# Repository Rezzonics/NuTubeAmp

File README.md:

# NuTubeAmp (EAGLE 6.3.0)
NuTube 6P1 25W Hybrid Amplifier

Eagle CAD 6.3.0:
- Eagle CAD Schematics (.sch)
- Eagle CAD Layout (.brd)
- Bill of Materials (txt, csv, xlsx)
- Components library (.lbr)

FreeCAD 16.0:
 - 3D CAD NuTube box (NuTube / 12AX7)

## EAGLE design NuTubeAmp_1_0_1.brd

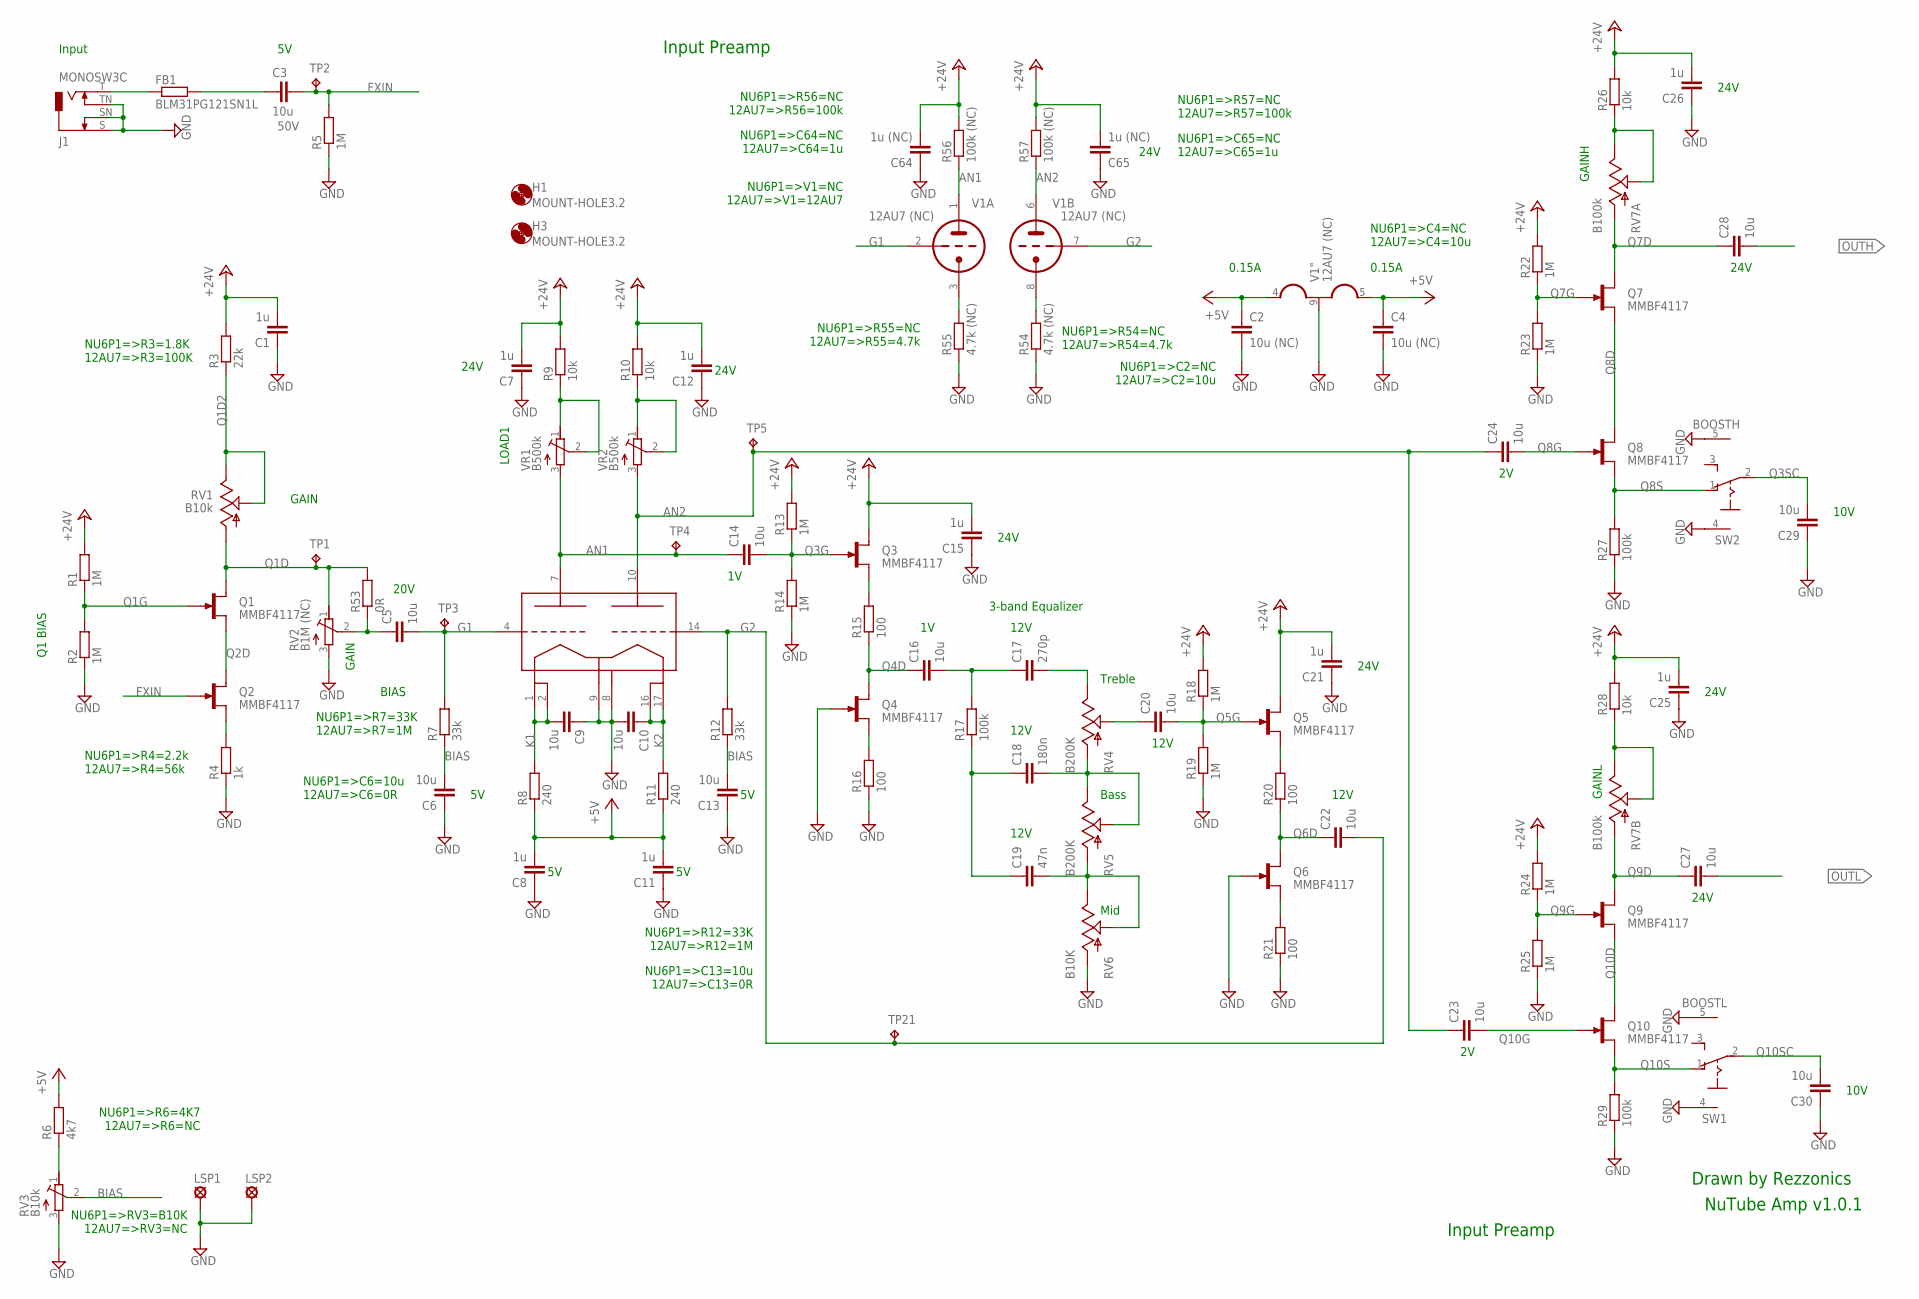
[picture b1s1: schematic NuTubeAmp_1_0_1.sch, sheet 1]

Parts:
C1, C7, C8, C11, C12, C15, C21, C25, C26: 1u; C0603K; MPN C1608X5R1H105K080AB
C2, C4: 10u (NC); C0805K; MPN GRM21BR6YA106KE43L
C3, C5, C6, C9, C10, C13, C14, C16, C20, C22, C23, C24, C27, C28, C29, C30: 10u; C0805K; MPN GRM21BR6YA106KE43L
C17: 270p; C0402K; MPN GRM1555C1H271JA01D
C18: 180n; C0603K; MPN GRM188R71C184KA01D
C19: 47n; C0402K; MPN GRM155R71H473KE14D
C64, C65: 1u (NC); C0603K; MPN C1608X5R1H105K080AB
FB1: BLM31PG121SN1L; R1206; MPN BLM31PG121SN1L
H1, H3: MOUNT-HOLE3.2; 3,2; MPN *
J1: MONOSW3C; NEUTRIK-NMJ4HCD2; MPN NMJ4HCD2
LSP1, LSP2: LSP13; MPN 1249
Q1, Q2, Q3, Q4, Q5, Q6, Q7, Q8, Q9, Q10: MMBF4117; SOT23; MPN MMBF4117
R1, R2, R5, R13, R14, R18, R19, R22, R23, R24, R25: 1M; R0402; MPN ERJ-2RKF1004X
R3: 22k; R0402; MPN ERJ-2RKF1801X
R4: 1k; R0402; MPN ERJ-2RKF2201X
R6: 4k7; R0402; MPN ERJ-2RKF4701X
R7, R12: 33k; R0402; MPN ERJ-2RKF3302X
R8, R11: 240; R0603; MPN ERJ-3EKF2400V
R9, R10, R26, R28: 10k; R0402; MPN ERJ-2RKF1002X
R15, R16, R20, R21: 100; R0402; MPN ERJ-2RKF1000X
R17, R27, R29: 100k; R0402; MPN ERJ-2RKF1003X
R53: 0R; R0402; MPN ERJ-2GE0R00X
R54, R55: 4.7k (NC); R0402; MPN ERJ-2RKF4701X
R56, R57: 100k (NC); R0402; MPN ERJ-2RKF1003X
RV1: B10k; 3310Y; MPN 3310Y-001-103L
RV2: B1M (NC); RTRIM3314G; MPN 3314G-1-105E
RV3: B10k; RTRIM3314G; MPN 3314G-2-103E
RV4, RV5: B200K; 3310Y; MPN 3310Y-001-204L
RV6: B10K; 3310Y; MPN 3310Y-001-103L
RV7: B100k; 3310H; MPN 3310H-001-104L
SW1: BOOSTL; MHS122K; MPN MHS122K
SW2: BOOSTH; MHS122K; MPN MHS122K
TP1, TP2, TP3, TP4, TP5, TP21: TPTP10R; TP10R; MPN *
U1: NUTUBE 6P1; NUTUBE_6P1_1; MPN *
V1: 12AU7 (NC); VT9; MPN *
VR1, VR2: B500k; RTRIM3314G; MPN 3314G-1-504E

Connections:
+5V: C2.1, C4.1, C8.2, C11.2, R6.2, R8.1, R11.1, V1.4 (H1), V1.5 (H3); also elsewhere on the board
+24V: C1.2, C7.2, C12.2, C15.2, C21.2, C25.2, C26.2, C64.2, C65.2, Q3.1 (D), Q5.1 (D), R1.2, R3.2, R9.2, R10.2, R13.2, R18.2, R22.2, R24.2, R26.2, R28.2, R56.2, R57.2; also elsewhere on the board
AN1: C14.1, R56.1, TP4.TP, U1.7 (A1_7), V1.1 (TA), VR1.3 (A)
AN2: C23.1, C24.1, R57.1, TP5.TP, U1.10 (A2_10), V1.6 (TA), VR2.3 (A)
BAST: C18.2, RV4.P$1 (A), RV5.P$2 (S), RV5.P$3 (E)
BIAS: C6.2, C13.2, R7.1, R12.1, RV3.2 (S)
EQIN: C16.2, C17.1, R17.2
EQOUT: C20.1, RV4.P$2 (S)
FXIN: C3.2, Q2.2 (G), R5.2, TP2.TP
G1: C5.2, R7.2, TP3.TP, U1.4 (G1_4), V1.2 (TG)
G2: C22.2, R12.2, TP21.TP, U1.14 (G2_14), V1.7 (TG)
G2TOP: R55.2, V1.3 (TK)
G3TOP: R26.1, RV7.P$2 (S), RV7.P$3 (E)
G4TOP: R28.1, RV7.P$5 (S), RV7.P$6 (E)
GND: C1.1, C2.2, C4.2, C6.1, C7.1, C8.1, C9.1, C10.2, C11.1, C12.1, C13.1, C15.1, C21.1, C25.1, C26.1, C29.1, C30.1, C64.1, C65.1, J1.S, J1.SN, J1.TN, LSP1.MP, LSP2.MP, Q4.2 (G), Q6.2 (G), R2.1, R4.1, R5.1, R14.1, R16.1, R19.1, R21.1, R23.1, R25.1, R27.1, R29.1, R54.1, R55.1, RV2.3 (A), RV3.3 (A), RV6.P$1 (A), SW1.4 (G1), SW1.5 (G2), SW2.4 (G1), SW2.5 (G2), U1.8 (GND_8), U1.9 (F2_9), V1.9 (H2); also elsewhere on the board
GTOP: C5.1, R53.1, RV2.2 (S)
K1: C9.2, R8.2, U1.1 (F1_1), U1.2 (F1_2)
K2: C10.1, R11.2, U1.16 (F3_16), U1.17 (F3_17)
MIDT: C19.2, RV5.P$1 (A), RV6.P$2 (S), RV6.P$3 (E)
unnamed: FB1.1, J1.T
unnamed: C3.1, FB1.2
unnamed: Q3.3 (S), R15.2
unnamed: R6.1, RV3.1 (E)
unnamed: R54.2, V1.8 (TK)
unnamed: C18.1, C19.1, R17.1
OUTH: C28.2; also elsewhere on the board
OUTL: C27.2; also elsewhere on the board
Q1D: Q1.1 (D), R53.2, RV1.P$1 (A), RV2.1 (E), TP1.TP
Q1D2: R3.1, RV1.P$2 (S), RV1.P$3 (E)
Q1G: Q1.2 (G), R1.1, R2.2
Q1S: Q2.3 (S), R4.2
Q1S1: Q4.3 (S), R16.2
Q1S2: Q6.3 (S), R21.2
Q2D: Q1.3 (S), Q2.1 (D)
Q3G: C14.2, Q3.2 (G), R13.1, R14.2
Q3SC: C29.2, SW2.2
Q4D: C16.1, Q4.1 (D), R15.1
Q5G: C20.2, Q5.2 (G), R18.1, R19.2
Q5S: Q5.3 (S), R20.2
Q6D: C22.1, Q6.1 (D), R20.1
Q7D: C28.1, Q7.1 (D), RV7.P$1 (A)
Q7G: Q7.2 (G), R22.1, R23.2
Q8D: Q7.3 (S), Q8.1 (D)
Q8G: C24.2, Q8.2 (G)
Q8S: Q8.3 (S), R27.2, SW2.1 (O)
Q9D: C27.1, Q9.1 (D), RV7.P$4 (A)
Q9G: Q9.2 (G), R24.1, R25.2
Q10D: Q9.3 (S), Q10.1 (D)
Q10G: C23.2, Q10.2 (G)
Q10S: Q10.3 (S), R29.2, SW1.1 (O)
Q10SC: C30.2, SW1.2
RL1: R9.1, VR1.1 (E), VR1.2 (S)
RL2: R10.1, VR2.1 (E), VR2.2 (S)
TBT: C17.2, RV4.P$3 (E)

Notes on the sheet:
NuTube Amp v1.0.1
Drawn by Rezzonics
Input Preamp
Treble
3-band Equalizer
Bass
Input
GAIN
Q1 BIAS
Mid
20V
24V
12V
10V
LOAD1
GAINH
GAINL
NU6P1=>R7=33K 12AU7=>R7=1M
BIAS
0.15A
NU6P1=>R3=1.8K 12AU7=>R3=100K
NU6P1=>R4=2.2k 12AU7=>R4=56k
NU6P1=>C6=10u 12AU7=>C6=0R
NU6P1=>V1=NC 12AU7=>V1=12AU7
NU6P1=>C64=NC 12AU7=>C64=1u
NU6P1=>R56=NC 12AU7=>R56=100k
NU6P1=>R57=NC 12AU7=>R57=100k
NU6P1=>C65=NC 12AU7=>C65=1u
NU6P1=>R55=NC 12AU7=>R55=4.7k
NU6P1=>R54=NC 12AU7=>R54=4.7k
NU6P1=>C2=NC 12AU7=>C2=10u
NU6P1=>C4=NC 12AU7=>C4=10u
NU6P1=>R12=33K 12AU7=>R12=1M
NU6P1=>C13=10u 12AU7=>C13=0R
NU6P1=>R6=4K7 12AU7=>R6=NC
NU6P1=>RV3=B10K 12AU7=>RV3=NC

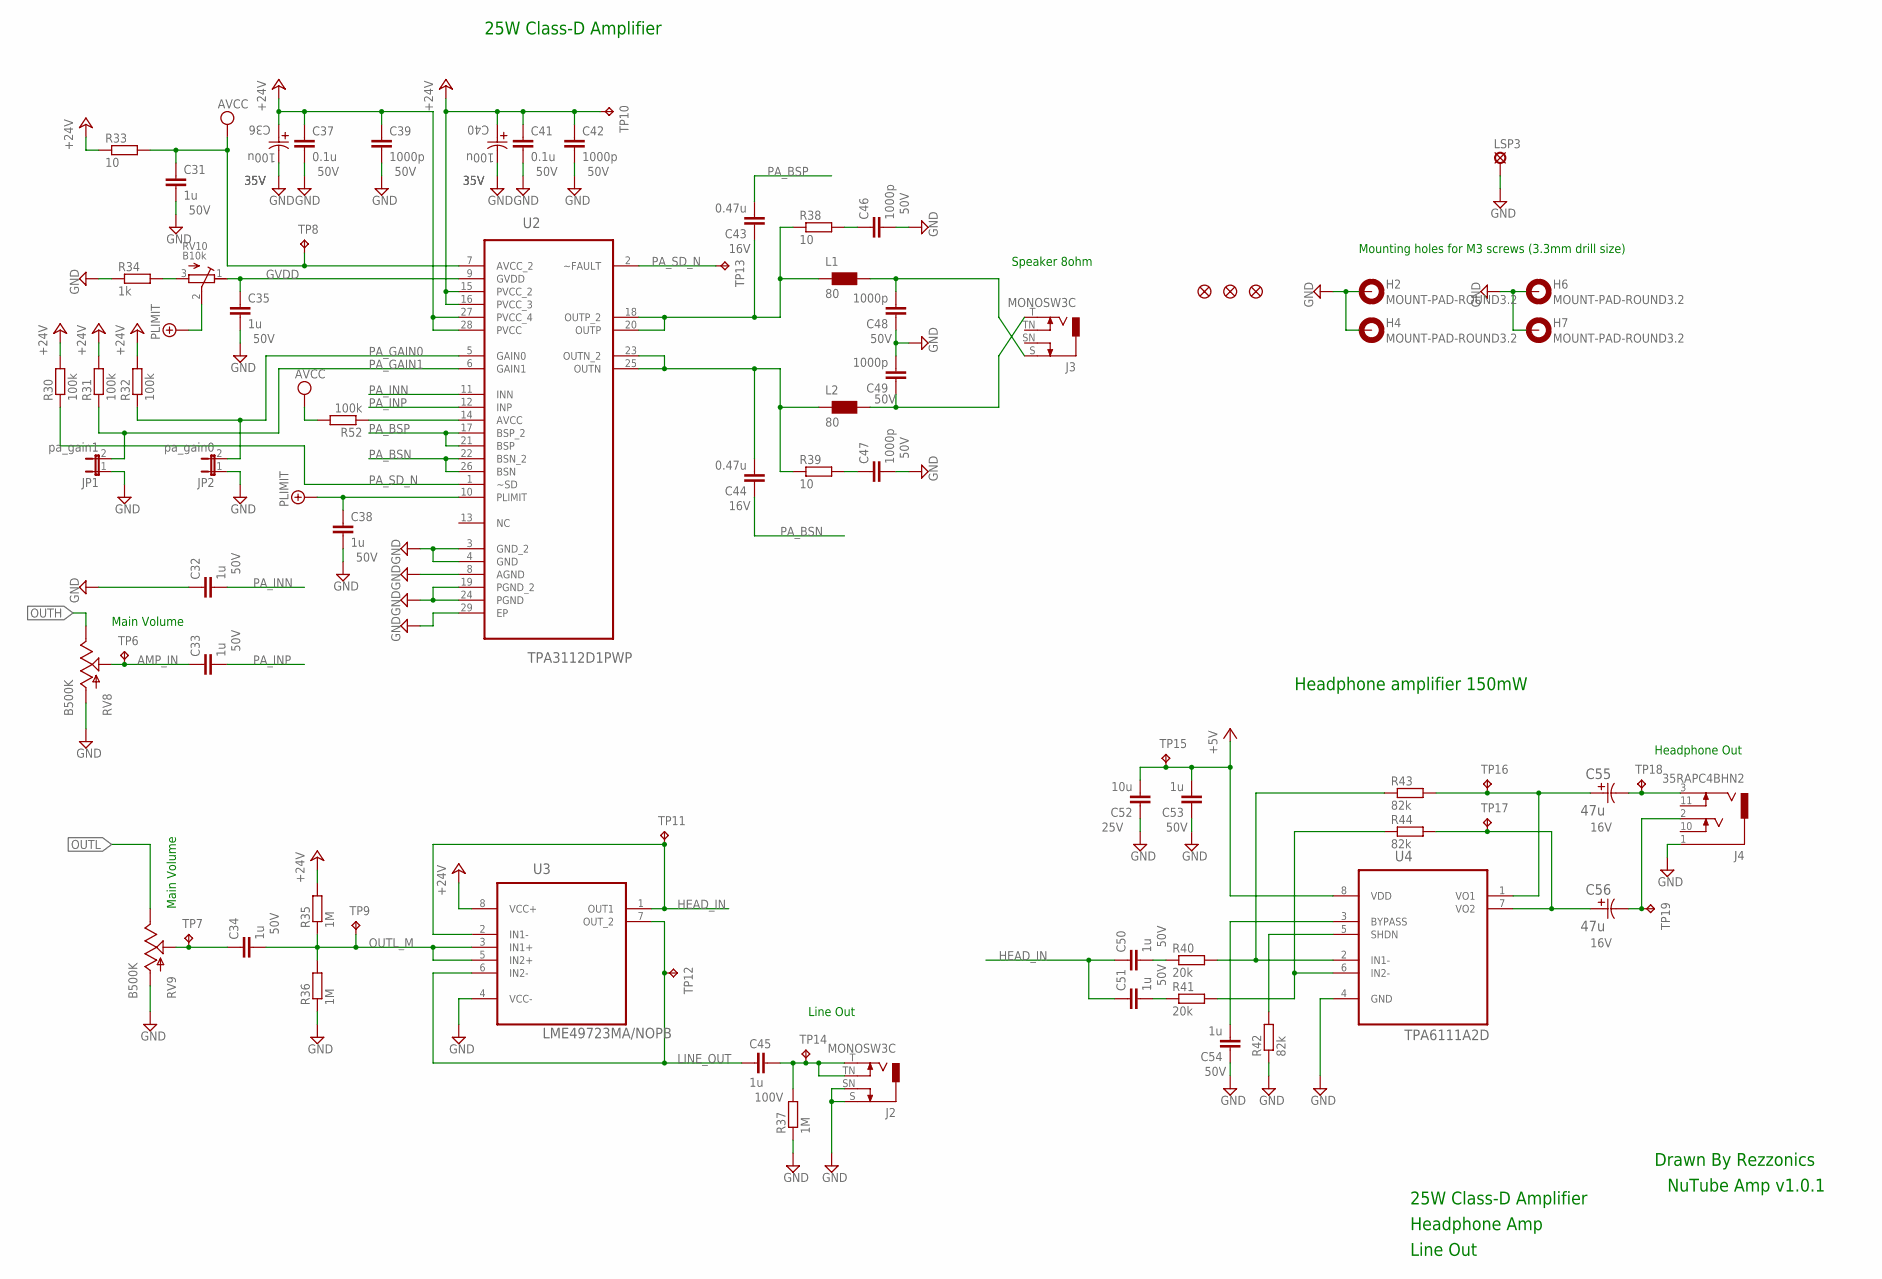
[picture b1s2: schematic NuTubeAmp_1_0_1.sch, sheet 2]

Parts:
C31, C32, C33, C34, C35, C38, C45, C50, C51, C53, C54: 1u; C0603K; MPN C1608X5R1H105K080AB
C36, C40: 100u; CAPAE660X800N; VOLTAGERATING 35V; MPN EEE-1VA101XP
C37, C41: 0.1u; C0603K; MPN GRM188R71H104KA93D
C39, C42, C46, C47, C48, C49: 1000p; C0603K; MPN GRM1885C1H102FA01D
C43, C44: 0.47u; C0603K; MPN GRM188R71C474KA88D
C52: 10u; C0805K; MPN GRM21BR6YA106KE43L
C55, C56: 47u; CAPAE530X610N; MPN EEE-HBC470UAR
H2, H4, H6, H7: MOUNT-PAD-ROUND3.2; 3,2-PAD; MPN *
J2, J3: MONOSW3C; NEUTRIK-NMJ4HCD2; MPN NMJ4HCD2
J4: 35RAPC4BHN2; MPN 35RAPC4BHN2
JP1: pa_gain1; 1X02; MPN 77311-401-36LF
JP2: pa_gain0; 1X02; MPN 77311-401-36LF
JP3, JP4, JP5: FIDUCIAL1X2.5; FIDUCIAL-1X2.5; MPN *
L1, L2: 80; 0805; MPN HI0805R800R-10
LSP3: LSP13; MPN 1249
R30, R31, R32, R52: 100k; R0603; MPN ERJ-3EKF1003V
R33, R38, R39: 10; R0603; MPN CRCW060310R0FKEAHP
R34: 1k; R0603; MPN ERJ-3EKF1001V
R35, R36, R37: 1M; R0402; MPN ERJ-2RKF1004X
R40, R41: 20k; R0603; MPN ERJ-3EKF2002V
R42, R43, R44: 82k; R0603; MPN ERJ-3EKF8202V
RV8, RV9: B500K; 3310Y; MPN 3310Y-001-504L
RV10: B10k; RTRIM3314G; MPN 3314G-2-103E
TP6, TP7, TP8, TP9, TP10, TP11, TP12, TP13, TP14, TP15, TP16, TP17, TP18, TP19: TPTP10R; TP10R; MPN *
U2: TPA3112D1PWP; SOP65P640X120-29N; MPN TPA3112D1PWP
U3: LME49723MA/NOPB; SOIC127P600X175-8N; MPN LME49723MA/NOPB
U4: TPA6111A2D; SOIC127P600X175-8N; MPN TPA6111A2D

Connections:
+5V: C52.2, C53.2, TP15.TP, U4.8 (VDD); also elsewhere on the board
+24V: C36.1, C37.1, C39.1, C40.1, C41.1, C42.1, R30.2, R31.2, R32.2, R33.1, R35.2, TP10.TP, U2.15 (PVCC_2), U2.16 (PVCC_3), U2.27 (PVCC_4), U2.28 (PVCC), U3.8 (VCC+); also elsewhere on the board
+UB: C38.1, RV10.2 (S), U2.10 (PLIMIT)
AMP_IN: C33.1, RV8.P$2 (S), TP6.TP
GND: C31.2, C32.1, C35.2, C36.2, C37.2, C38.2, C39.2, C40.2, C41.2, C42.2, C46.2, C47.2, C48.1, C49.2, C52.1, C53.1, C54.1, H2.B3,2, H4.B3,2, H6.B3,2, H7.B3,2, J2.S, J2.SN, J4.1 (S), JP1.1, JP2.1, LSP3.MP, R34.1, R36.1, R37.1, R42.1, RV8.P$1 (A), RV9.P$1 (A), U2.3 (GND_2), U2.4 (GND), U2.8 (AGND), U2.19 (PGND_2), U2.24 (PGND), U2.29 (EP), U3.4 (VCC-), U4.4 (GND); also elsewhere on the board
GVDD: C35.1, RV10.1 (E), U2.9 (GVDD)
HEAD_IN: C50.1, C51.1, TP11.TP, U3.1 (OUT1), U3.2 (IN1-)
LINE_OUT: C45.1, TP12.TP, U3.6 (IN2-), U3.7 (OUT_2)
unnamed: R40.2, R43.1, U4.2 (IN1-)
unnamed: R52.1, U2.14 (AVCC)
unnamed: R41.2, R44.1, U4.6 (IN2-)
unnamed: C55.1, R43.2, TP16.TP, U4.1 (VO1)
unnamed: C34.1, RV9.P$2 (S), TP7.TP
unnamed: C56.1, R44.2, TP17.TP, U4.7 (VO2)
unnamed: C50.2, R40.1
unnamed: C51.2, R41.1
unnamed: C54.2, U4.3 (BYPASS)
unnamed: R42.2, U4.5 (SHDN)
unnamed: C55.2, J4.3 (R), TP18.TP
unnamed: C56.2, J4.2 (T), TP19.TP
unnamed: C45.2, J2.T, J2.TN, R37.2, TP14.TP
unnamed: C46.1, R38.2
unnamed: C47.1, R39.2
unnamed: R34.2, RV10.3 (A)
unnamed: C49.1, J3.T, L2.2
unnamed: C48.2, J3.S, L1.2
unnamed: C43.1, L1.1, R38.1, U2.18 (OUTP_2), U2.20 (OUTP)
unnamed: C44.2, L2.1, R39.1, U2.23 (OUTN_2), U2.25 (OUTN)
OUTH: RV8.P$3 (E); also elsewhere on the board
OUTL: RV9.P$3 (E); also elsewhere on the board
OUTL_M: C34.2, R35.1, R36.2, TP9.TP, U3.3 (IN1+), U3.5 (IN2+)
PA_BSN: C44.1, U2.22 (BSN_2), U2.26 (BSN)
PA_BSP: C43.2, U2.17 (BSP_2), U2.21 (BSP)
PA_GAIN0: JP2.2, R32.1, U2.5 (GAIN0)
PA_GAIN1: JP1.2, R31.1, U2.6 (GAIN1)
PA_INN: C32.2, U2.11 (INN)
PA_INP: C33.2, U2.12 (INP)
PA_SD_N: R30.1, TP13.TP, U2.1 (~SD), U2.2 (~FAULT)
VCC: C31.1, R33.2, R52.2, TP8.TP, U2.7 (AVCC_2)

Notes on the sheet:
Drawn By Rezzonics
NuTube Amp v1.0.1
Speaker 8ohm
25W Class-D Amplifier
Mounting holes for M3 screws (3.3mm drill size)
Headphone amplifier 150mW
Headphone Out
Main Volume
Headphone Amp
Line Out

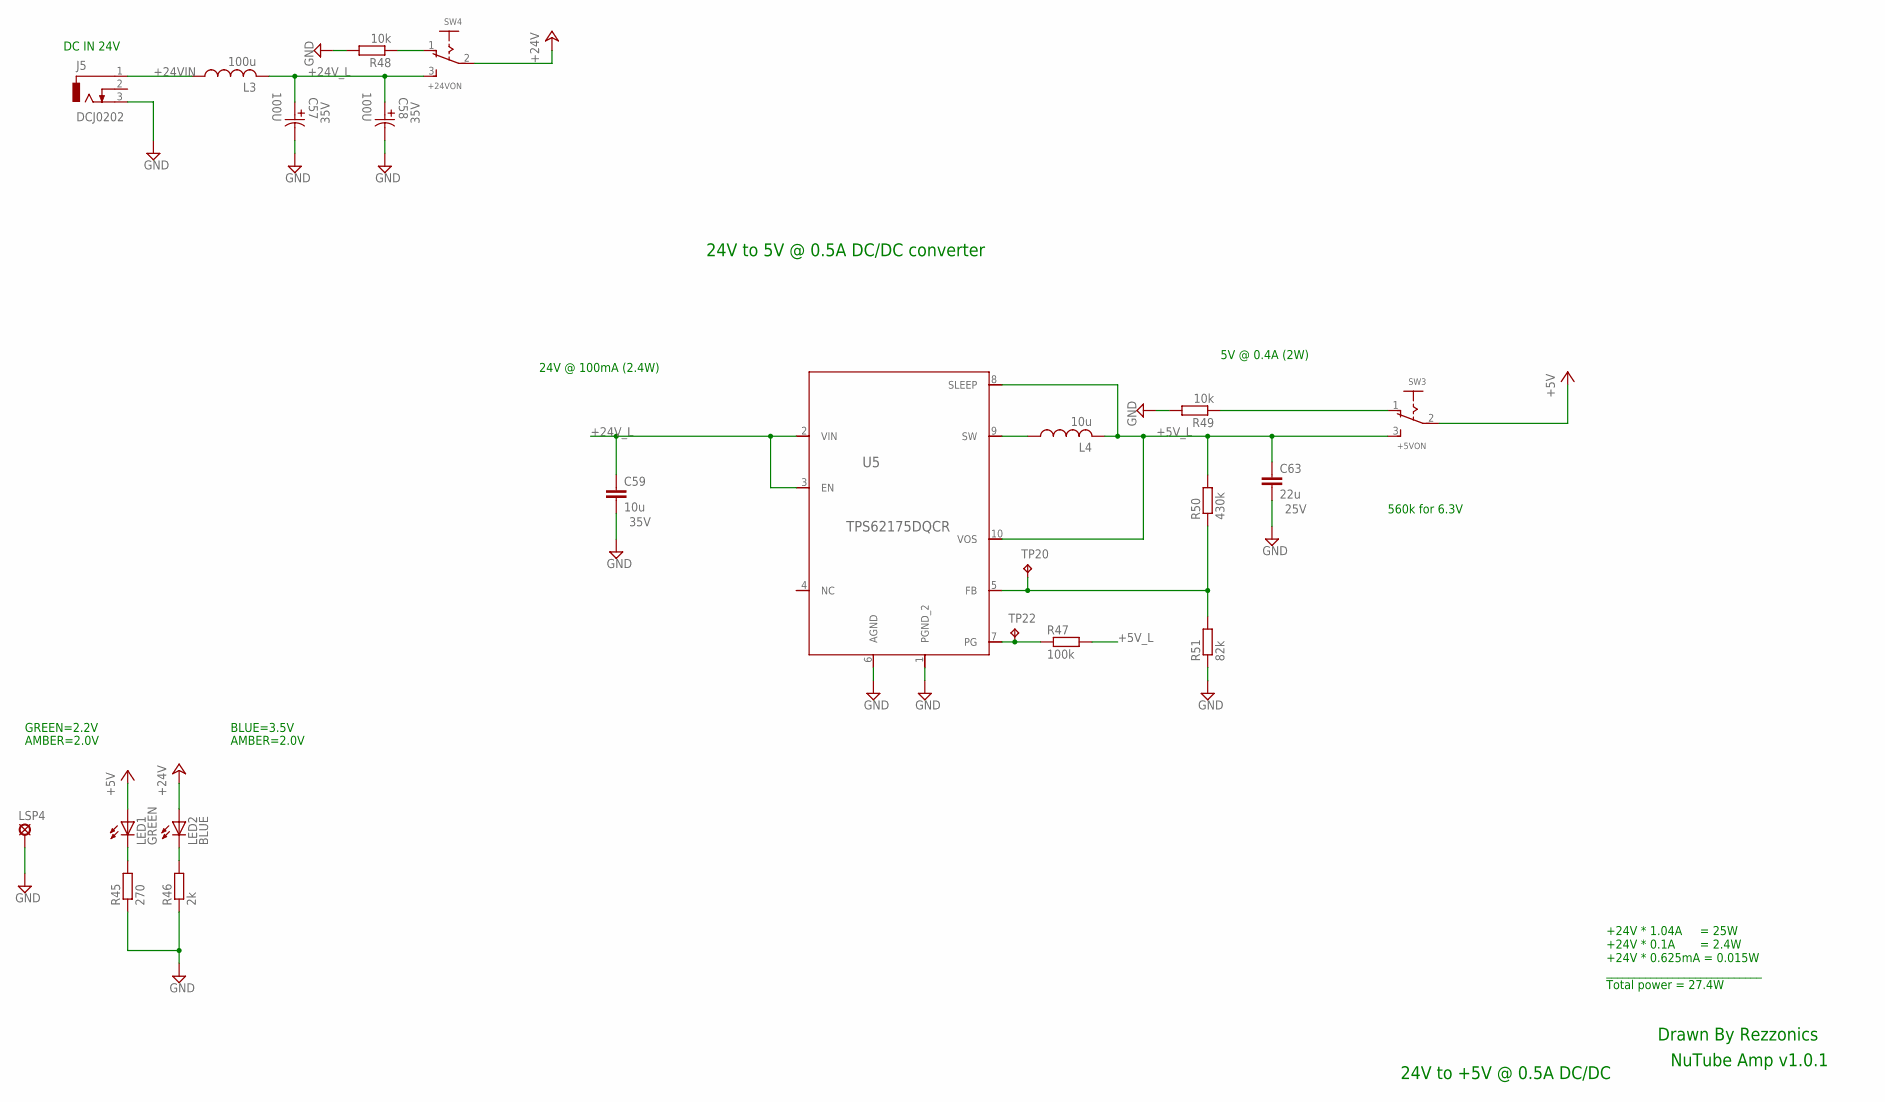
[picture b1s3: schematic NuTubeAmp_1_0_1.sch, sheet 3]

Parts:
C57, C58: 100U; CAPAE660X800N; VOLTAGERATING 35V; MPN EEE-1VA101XP
C59: 10u; C0805K; MPN GRM21BR6YA106KE43L
C63: 22u; C0805K; MPN C2012X5R1V226M125AC
J5: DCJ0202; MPN PJ-202A
L3: 100u; SRN1060; MPN SRN1060-101M
L4: 10u; SRN4018; MPN SRN4018-100M
LED1: GREEN; LED5MM; MPN SSL-LX5093GD
LED2: BLUE; LED5MM; MPN SSL-LX5093USBD
LSP4: LSP13; MPN 1249
R45: 270; R0603; MPN ERJ-PA3F2700V
R46: 2k; R0603; MPN ERJ-PA3F2001V
R47: 100k; R0402; MPN ERJ-2RKF1003X
R48, R49: 10k; R0603; MPN CR0603-FX-1002HLF
R50: 430k; R0402; MPN ERJ-2GEJ434X
R51: 82k; R0402; MPN ERJ-2RKF8202X
SW3: +5VON; GH39P0; MPN GH36P010001
SW4: +24VON; GH39P0; MPN GH36P010001
TP20, TP22: TPTP10R; TP10R; MPN *
U5: TPS62175DQCR; R-PWSON-N10; MPN TPS62175DQCR

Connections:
+5V: LED1.A, SW3.2; also elsewhere on the board
+5V_L: C63.1, L4.2, R47.2, R50.2, SW3.3 (S), U5.8 (SLEEP), U5.10 (VOS)
+24V: LED2.A, SW4.2; also elsewhere on the board
+24VIN: J5.1, L3.1
+24V_L: C57.1, C58.1, C59.1, L3.2, SW4.3 (S), U5.2 (VIN), U5.3 (EN)
GND: C57.2, C58.2, C59.2, C63.2, J5.3, LSP4.MP, R45.1, R46.1, R48.2, R49.2, R51.1, U5.1 (PGND_2), U5.6 (AGND); also elsewhere on the board
unnamed: R47.1, TP22.TP, U5.7 (PG)
unnamed: R48.1, SW4.1 (O)
unnamed: R49.1, SW3.1 (O)
unnamed: L4.1, U5.9 (SW)
unnamed: LED1.K (C), R45.2
unnamed: LED2.K (C), R46.2
VCC3: R50.1, R51.2, TP20.TP, U5.5 (FB)

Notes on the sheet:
24V @ 100mA (2.4W)
24V to 5V @ 0.5A DC/DC converter
5V @ 0.4A (2W)
Drawn By Rezzonics
NuTube Amp v1.0.1
24V to +5V @ 0.5A DC/DC
+24V * 1.04A = 25W +24V * 0.1A = 2.4W +24V * 0.625mA = 0.015W ____________________________ Total power = 27.4W
DC IN 24V
560k for 6.3V
GREEN=2.2V
BLUE=3.5V
AMBER=2.0V

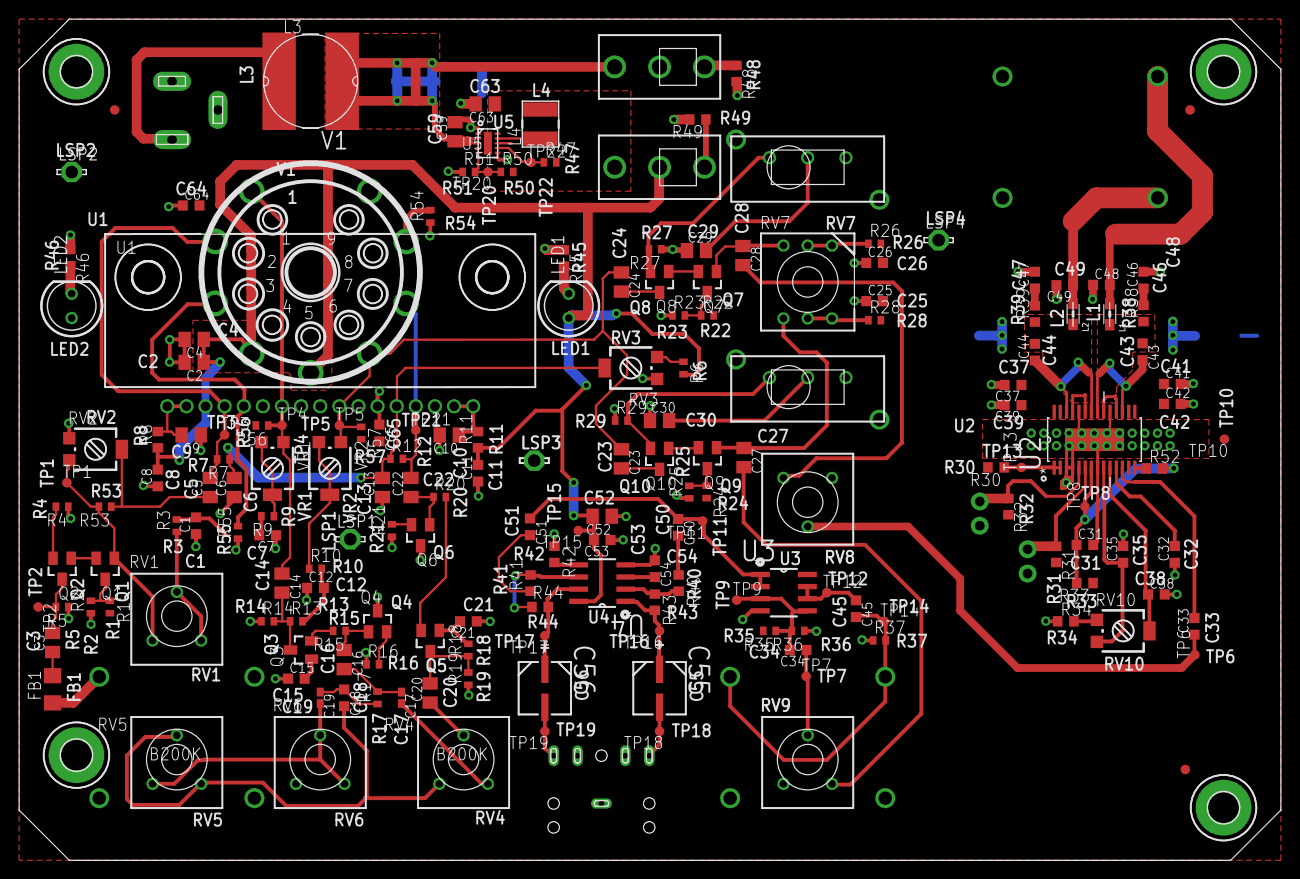
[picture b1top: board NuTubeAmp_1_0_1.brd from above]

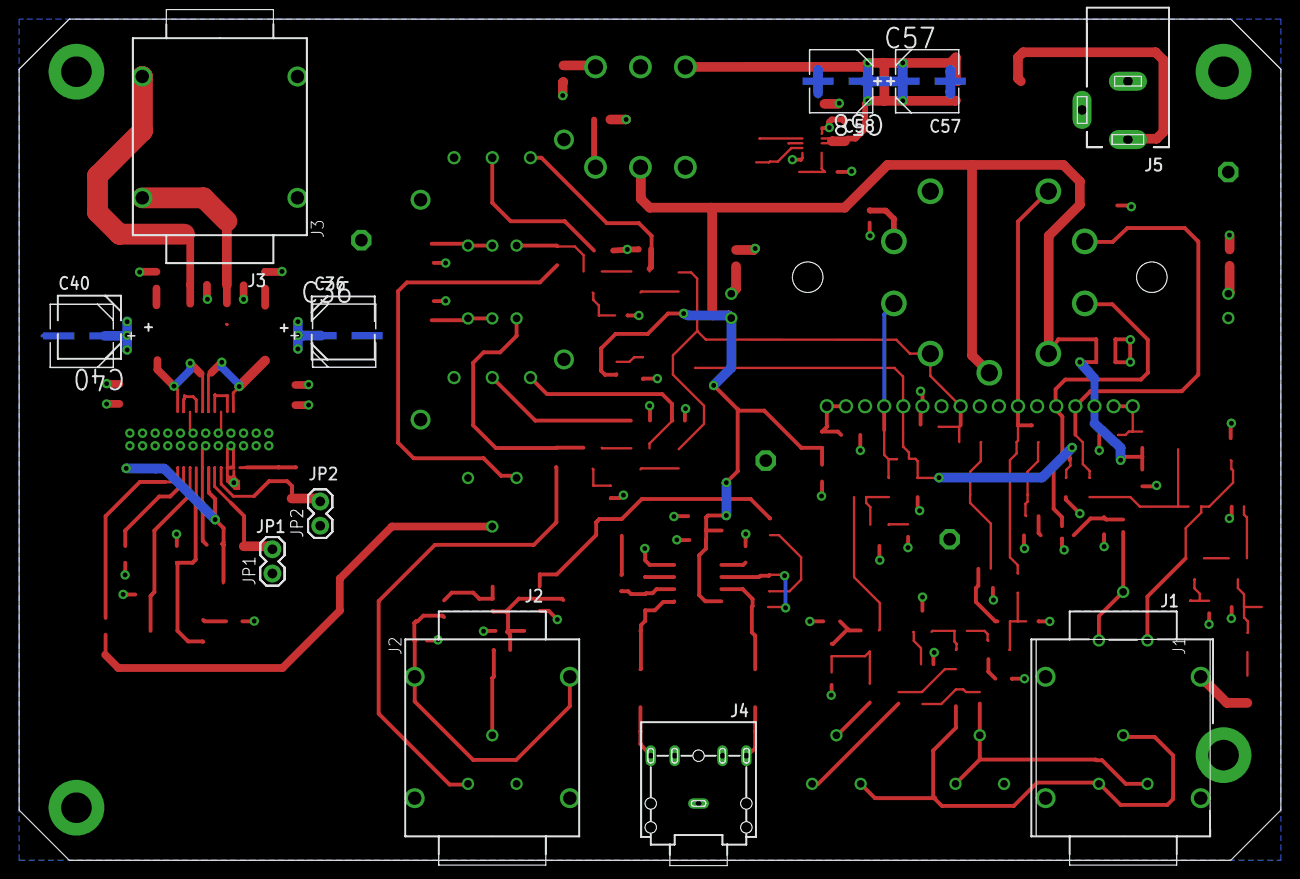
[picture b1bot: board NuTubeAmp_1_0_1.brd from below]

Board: 2 copper layers, 132.0 x 88.0 mm, 200 parts (11 on the bottom side), 98 nets.

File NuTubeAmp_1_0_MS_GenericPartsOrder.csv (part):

Part Number,Mfg Name,VID,Vendor Part Num,Description,Customer Ref,Part Value,Tol,Qty-1,Qty-5,Qty-25,Part References,Value
GH36P010001,APEM Inc.,ME,642-GH36P010001,SWITCH SLIDE SPDT 3A 30V,con023,GH36P010001,*,2,10,50,"SW3, SW4",
GRM188R71H104KA93D,Murata,ME,81-GRM39X104K50D,CAP CER 0.1UF 50V X7R 0603,capcer012,100n,*,2,10,50,"C37, C41",0.1u
GRM188R71C474KA88D,Murata,ME,81-GRM188R71C474KA88,Multilayer Ceramic Capacitors MLCC - SMD/SMT 0603 0.47uF 16volts X7R 10%,capcer013,470n,*,2,10,50,"C43, C44",0.47u
ERJ-2GE0R00X,Panasonic,ME,667-ERJ-2GE0R00X,RES SMD 0.0 OHM JUMPER 1/10W 0402,res074,0R,*,3,15,75,"R53, R59, R60",0R
ERJ-2GE0R00X,Panasonic,ME,667-ERJ-2GE0R00X,RES SMD 0.0 OHM JUMPER 1/10W 0402,res074,0R,*,1,5,25,"R58",0R  (NC)
ERJ-2RKF1801X,Panasonic,ME,667-ERJ-2RKF1801X,RES SMD 1.8K OHM 1% 1/10W 0402,res110,1.8k,*,1,5,25,"R3",1.8k
ERJ-2RKF1004X,Panasonic,ME,667-ERJ-2RKF1004X,Thick Film Resistors - SMD 0402 1Mohms 1%,res076,1M,*,14,70,350,"R1, R2, R5, R13, R14, R18, R19, R22, R23, R24, R25, R35, R36, R37",1M
ERJ-3EKF1001V,Panasonic,ME,667-ERJ-3EKF1001V,Thick Film Resistors - SMD 0603 1Kohms 1% Tol,res018,1k,*,1,5,25,"R34",1k
C1608X5R1H105K080AB,TDK,ME,810-C1608X5R1H105K,CAP CER 1UF 50V X5R 0603,capcer028,1u,*,20,100,500,"C1, C7, C8, C11, C12, C15, C21, C25, C26, C31, C32, C33, C34, C35, C38, C45, C50, C51, C53, C54",1u
C1608X5R1H105K080AB,TDK,ME,810-C1608X5R1H105K,CAP CER 1UF 50V X5R 0603,capcer028,1u,*,2,10,50,"C64, C65",1u (NC)
ERJ-2RKF2201X,Panasonic,ME,667-ERJ-2RKF2201X,Thick Film Resistors - SMD 0402 2.2Kohms 1%,res078,2.2k,*,1,5,25,"R4",2.2k
ERJ-PA3F2001V,Panasonic,ME,667-ERJ-PA3F2001V,RES SMD 2K OHM 1% 1/4W 0603,res126,2k,*,1,5,25,"R46",2k
ERJ-2RKF4701X,Panasonic,ME,667-ERJ-2RKF4701X,Thick Film Resistors - SMD 0402 4.7Kohms 1%,res080,4.7k,*,2,10,50,"R54, R55",4.7k (NC)
ERJ-2RKF4701X,Panasonic,ME,667-ERJ-2RKF4701X,Thick Film Resistors - SMD 0402 4.7Kohms 1%,res080,4.7k,*,1,5,25,"R6",4k7
CRCW060310R0FKEAHP,Vishay,ME,71-CRCW060310R0FKEAH,Thick Film Resistors - SMD 1/4watt 10ohms 1% 100ppm High Power,res033,10,*,3,15,75,"R33, R38, R39",10
CR0603-FX-1002HLF,Bourns,ME,652-CR0603-FX1002HLF,Thick Film Resistors - SMD 10KOHM 1/10WATT 1%,res002,10k,*,2,10,50,"R48, R49",10k
ERJ-2RKF1002X,Panasonic,ME,667-ERJ-2RKF1002X,Thick Film Resistors - SMD 0402 10Kohms 1%,res083,10k,*,4,20,100,"R9, R10, R26, R28",10k
GRM21BR6YA106KE43L,Murata,ME,81-GRM21BR6YA106KE3L,CAP CER 10UF 35V X5R 0805,capcer075,10u,*,18,90,450,"C3, C5, C6, C9, C10, C13, C14, C16, C20, C22, C23, C24, C27, C28, C29, C30, C52, C59",10u
SRN4018-100M,Bourns,ME,652-SRN4018-100M,FIXED IND 10UH 1.3A 180 MOHM SMD,ind010,10u,*,1,5,25,"L4",10u
GRM21BR6YA106KE43L,Murata,ME,81-GRM21BR6YA106KE3L,CAP CER 10UF 35V X5R 0805,capcer075,10u,*,2,10,50,"C2, C4",10u (NC)
*** ERROR - PART '*' NOT FOUND FOR: "V1"
ERJ-3EKF2002V,Panasonic,ME,667-ERJ-3EKF2002V,RES SMD 20K OHM 1% 1/10W 0603,res022,20k,*,2,10,50,"R40, R41",20k
C2012X5R1V226M125AC,TDK,ME,810-C2012X5R1V226MAC,CAP CER 22UF 35V X5R 0805,capcer078,22u,*,1,5,25,"C63",22u
ERJ-2RKF3302X,Panasonic,ME,667-ERJ-2RKF3302X,RES SMD 33K OHM 1% 1/10W 0402,res091,33k,*,2,10,50,"R7, R12",33k
35RAPC4BHN2,Switchcraft,ME,502-35RAPC4BHN2,Phone Connectors 3C 3.5mm JACKET,con008,35RAPC4BHN2,*,1,5,25,"J4",35RAPC4BHN2
GRM155R71H473KE14D,Murata,ME,81-GRM155R71H473KE4D,CAP CER 0.047UF 50V 10% X7R 0402,capcer058,47n,*,1,5,25,"C19",47n
EEE-HBC470UAR,Panasonic,ME,667-EEE-HBC470UAR,CAP ALUM 47UF 20% 16V SMD,capelec003,47u,*,2,10,50,"C55, C56",47u
HI0805R800R-10,Laird Technologies,ME,875-HI0805R800R-10,EMI Filter Beads, Chips & Arrays 80ohms 100MHz 5A Monolithic 0805 SMD,fer003,80,*,2,10,50,"L1, L2",80
ERJ-2RKF8202X,Panasonic,ME,667-ERJ-2RKF8202X,RES SMD 82K OHM 1% 1/10W 0402,res108,82k,*,1,5,25,"R51",82k
ERJ-3EKF8202V,Panasonic,ME,667-ERJ-3EKF8202V,RES SMD 82K OHM 1% 1/10W 0603,res042,82k,*,3,15,75,"R42, R43, R44",82k
ERJ-2RKF1000X,Panasonic,ME,667-ERJ-2RKF1000X,RES SMD 100 OHM 1% 1/10W 0402,res094,100,*,4,20,100,"R15, R16, R20, R21",100
EEE-1VA101XP,Panasonic,ME,667-EEE-1VA101XP,CAP ALUM 100UF 20% 35V SMD,capelec002,100u,*,2,10,50,"C57, C58",100U
ERJ-2RKF1003X,Panasonic,ME,667-ERJ-2RKF1003X,Thick Film Resistors - SMD 0402 100Kohms 1%,res095,100k,*,4,20,100,"R17, R27, R29, R47",100k
ERJ-3EKF1003V,Panasonic,ME,667-ERJ-3EKF1003V,RES SMD 100K OHM 1% 1/10W 0603,res048,100k,*,3,15,75,"R30, R31, R32",100k
ERJ-2RKF1003X,Panasonic,ME,667-ERJ-2RKF1003X,Thick Film Resistors - SMD 0402 100Kohms 1%,res095,100k,*,2,10,50,"R56, R57",100k (NC)
EEE-1VA101XP,Panasonic,ME,667-EEE-1VA101XP,CAP ALUM 100UF 20% 35V SMD,capelec002,100u,*,2,10,50,"C36, C40",100u
SRN1060-101M,Bourns,ME,652-SRN1060-101M,FIXED IND 100UH 1.7A 210 MOHM,ind009,100u,*,1,5,25,"L3",100u
GRM188R71C184KA01D,Murata,ME,81-GRM188R71C184KA1D,CAP CER 0.18UF 16V X7R 0603,capcer077,180n,*,1,5,25,"C18",180n
ERJ-3EKF2400V,Panasonic,ME,667-ERJ-3EKF2400V,RES SMD 240 OHM 1% 1/10W 0603,res121,240,*,2,10,50,"R8, R11",240
ERJ-PA3F2700V,Panasonic,ME,667-ERJ-PA3F2700V,RES SMD 270 OHM 1% 1/4W 0603,res127,270,*,1,5,25,"R45",270
GRM1555C1H271JA01D,Murata,ME,81-GRM155C1H271JA01D,CAP CER 270PF 50V NP0 0402,capcer073,270p,*,1,5,25,"C17",270p
ERJ-2GEJ434X,Panasonic,ME,667-ERJ-2GEJ434X,RES SMD 430K OHM 5% 1/10W 0402,res124,430k,*,1,5,25,"R50",430k
GRM1885C1H102FA01D,Murata,ME,81-GRM1885C1H102FA1D,CAP CER 1000PF 50V C0G/NP0 0603,capcer017,1n,*,6,30,150,"C39, C42, C46, C47, C48, C49",1000p
3314G-1-105E,Bourns,ME,652-3314G-1-105E,TRIMMER 1M OHM 0.25W SMD,pottrim003,B1M,*,1,5,25,"RV2",B1M (NC)
3310Y-001-103L,Bourns,ME,652-3310Y-001-103L,POT 10K OHM 1/4W PLASTIC LINEAR,pot018,B10K,*,1,5,25,"RV6",B10K
3310Y-001-103L,Bourns,ME,652-3310Y-001-103L,POT 10K OHM 1/4W PLASTIC LINEAR,pot018,B10K,*,1,5,25,"RV1",B10k
3314G-2-103E,Bourns,ME,652-3314G-2-103E,TRIMMER 10K OHM 0.25W SMD,pottrim005,B10k,*,2,10,50,"RV3, RV10",B10k
3310H-001-104L,Bourns,ME,652-3310H-001-104L,POT 100K OHM 1/4W PLASTIC LINEAR 9mm,pot018,B100K,*,1,5,25,"RV7",B100k
3310Y-001-204L,Bourns,ME,652-3310Y-001-204L,Potentiometers 9mm 200Kohms Single Cup,pot015,B200k,*,2,10,50,"RV4, RV5",B200K
3310Y-001-504L,Bourns,ME,652-3310Y-001-504L,Potentiometers 9mm 500Kohms Single Cup,pot016,B500k,*,2,10,50,"RV8, RV9",B500K
3314G-1-504E,Bourns,ME,652-3314G-1-504E,TRIMMER 500K OHM 0.25W SMD,pottrim003,B500k,*,2,10,50,"VR1, VR2",B500k
BLM31PG121SN1L,Murata,ME,81-BLM31PG121SN1L,EMI Filter Beads, Chips & Arrays 1206 120 OHM,fer002,120,*,1,5,25,"FB1",BLM31PG121SN1L
SSL-LX5093USBD,Lumex,ME,696-SSL-LX5093USBD,LED BLUE DIFF 5MM ROUND T/H,led009,Blue,*,1,5,25,"LED2",BLUE
MHS122K,APEM Inc.,ME,642-MHS122K,SWITCH SLIDE SPDT 300MA 30V,sw0013,MHS122K,*,1,5,25,"SW2",BOOSTH
MHS122K,APEM Inc.,ME,642-MHS122K,SWITCH SLIDE SPDT 300MA 30V,sw0013,MHS122K,*,1,5,25,"SW1",BOOSTL
PJ-202A,CUI,ME,490-PJ-202A,CONN POWER JACK 2.1MM PCB,con014,PJ-202A,*,1,5,25,"J5",DCJ0202
*** ERROR - PART '*' NOT FOUND FOR: "JP3, JP4, JP5"
SSL-LX5093GD,Lumex,ME,696-SSL-LX5093GD,LED GRN DIFF 5MM ROUND T/H,led010,Green,*,1,5,25,"LED1",GREEN
LME49723MA/NOPB,Texas Instruments,ME,926-LME49723MA/NOPB,Audio Amplifiers Dual Audio Op Amp,icopamp002,LME49723,*,1,5,25,"U3",LME49723MA/NOPB
1249,Keystone electronics,ME,534-1249,Test Points TP TERM BRS MATTE TINNED PLATED,tp001,*,*,4,20,100,"LSP1, LSP2, LSP3, LSP4",LSP13
MMBF4117,Fairchild Semiconductor,ME,512-MMBF4117,JFET N-CH 40V 0.225W SOT23,jfet002,MMBF4117,*,10,50,250,"Q1, Q2, Q3, Q4, Q5, Q6, Q7, Q8, Q9, Q10",MMBF4117
NMJ4HCD2,REAN,ME,550-12202,Phone Connectors 2C MONO 2-SPST NC,con005,*,*,3,15,75,"J1, J2, J3",MONOSW3C
*** ERROR - PART '*' NOT FOUND FOR: "H1, H3"
*** ERROR - PART '*' NOT FOUND FOR: "H2, H4, H6, H7"
*** ERROR - PART '*' NOT FOUND FOR: "U1"
TPA3112D1PWP,Texas Instruments,ME,595-TPA3112D1PWP,Audio Amplifiers 25W Filter-Free Mono Class-D Aud Amp,icamp003,TP3112D,*,1,5,25,"U2",TPA3112D1PWP
TPA6111A2D,Texas Instruments,ME,595-TPA6111A2D,Audio Amplifiers Stereo HdPhne Aud,icamp002,TP6111A,*,1,5,25,"U4",TPA6111A2D
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

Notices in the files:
parts and their libraries:
SparkFun: Licensing: CC v3.0 Share-Alike You are welcome to use this library for commercial purposes.
wuerth-elektronik: Copyright: Würth Elektronik eiSos
